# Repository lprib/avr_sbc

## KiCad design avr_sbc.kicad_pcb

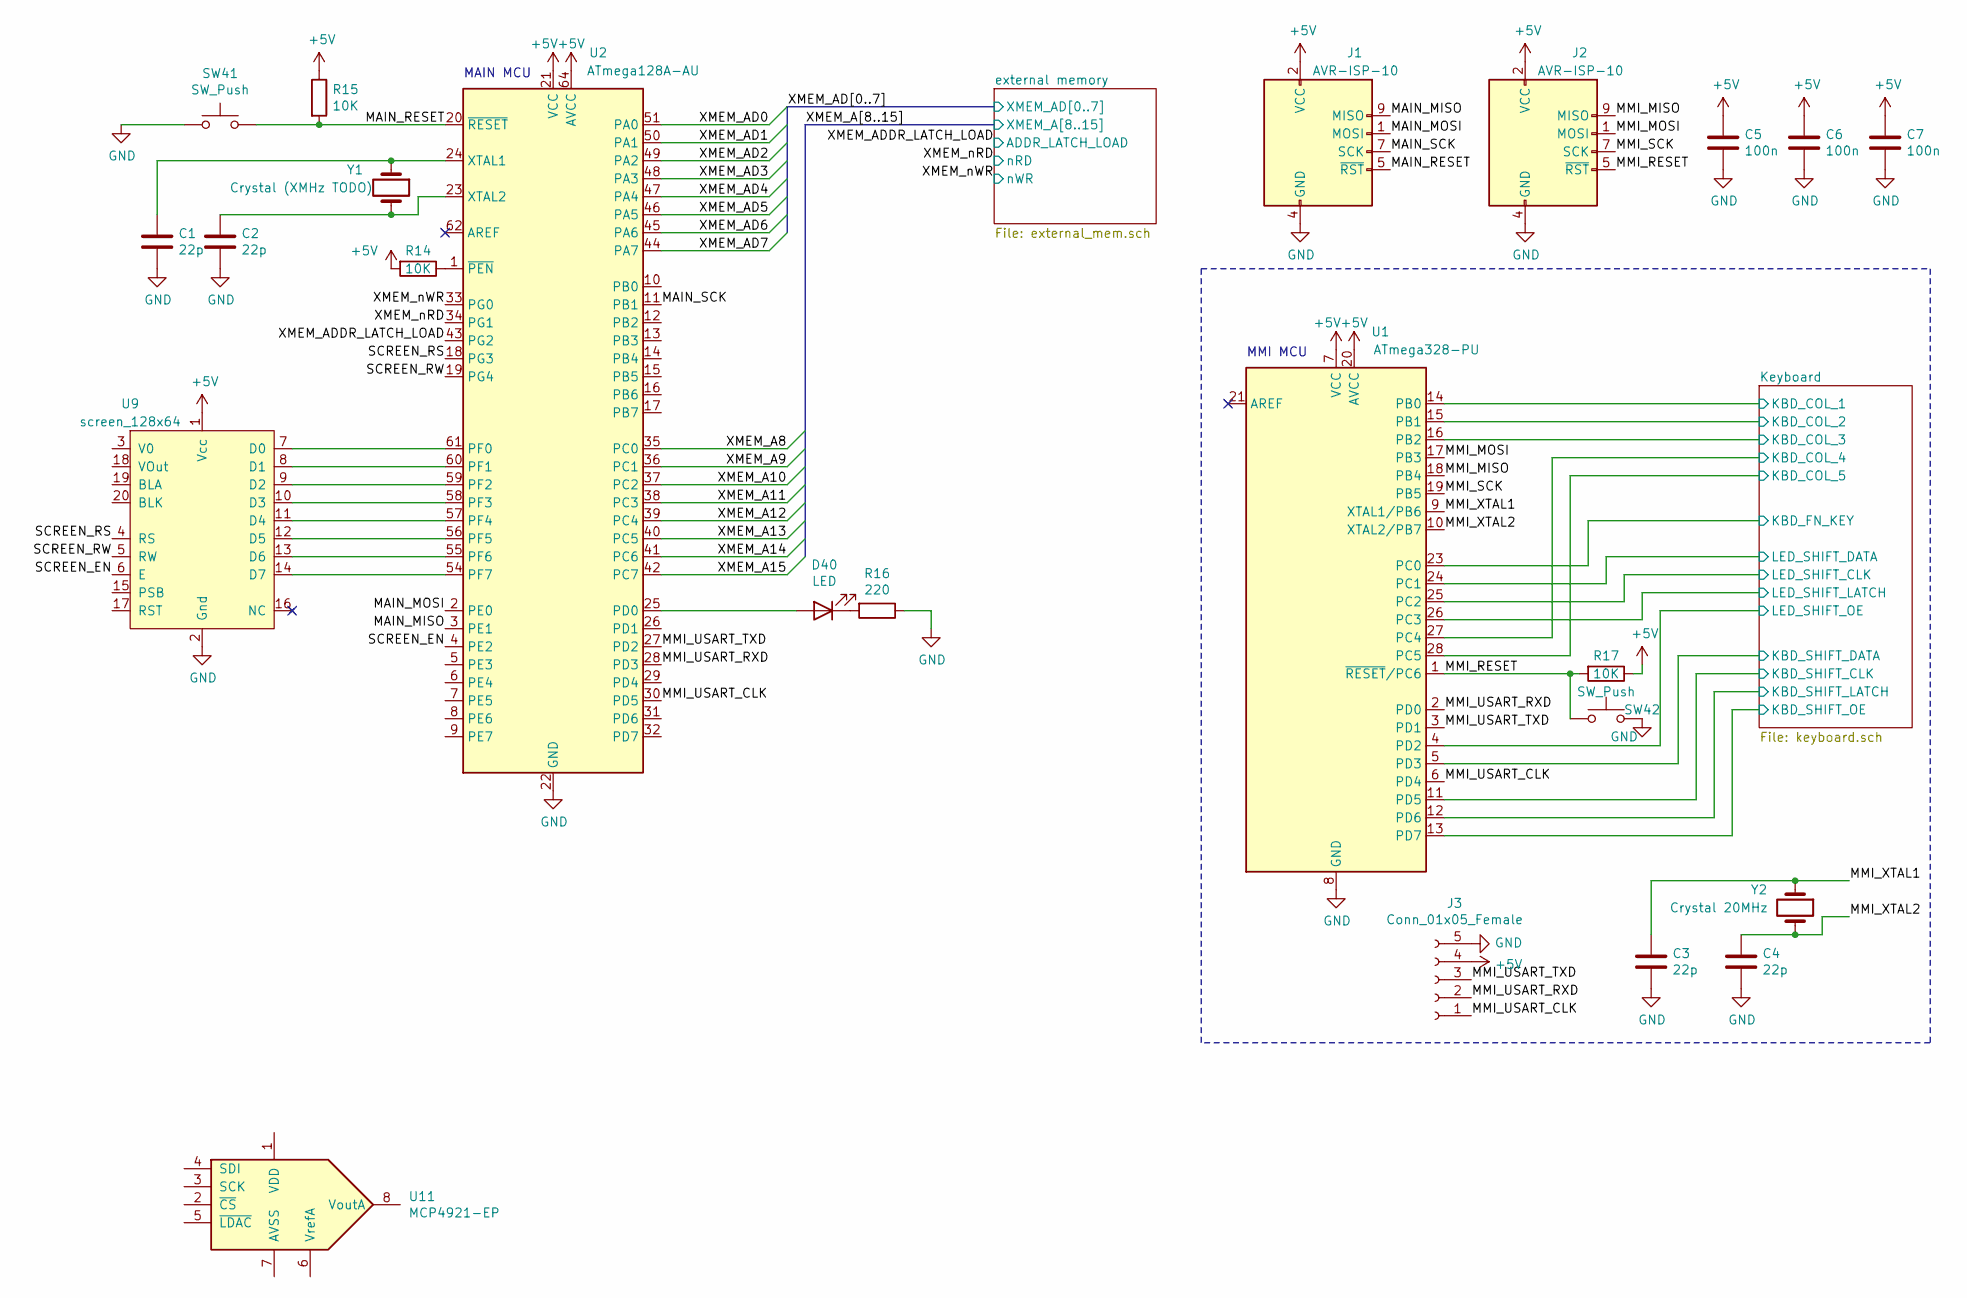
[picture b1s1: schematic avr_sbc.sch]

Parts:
C1, C2, C3, C4: 22p; C_Disc_D3.0mm_W1.6mm_P2.50mm
C5, C6, C7: 100n; C_Disc_D3.0mm_W1.6mm_P2.50mm
D40: LED; LED_D5.0mm
J1, J2: AVR-ISP-10; PinHeader_2x05_P2.54mm_Vertical
J3: Conn_01x05_Female; PinHeader_1x05_P2.54mm_Vertical
R14, R15, R17: 10K; R_Axial_DIN0207_L6.3mm_D2.5mm_P7.62mm_Horizontal
R16: 220; R_Axial_DIN0207_L6.3mm_D2.5mm_P7.62mm_Horizontal
SW41, SW42: SW_Push; SW_PUSH_6mm
U1: ATmega328-PU; DIP-28_W7.62mm
U2: ATmega128A-AU; TQFP-64_14x14mm_P0.8mm
U9: screen_128x64; PinHeader_1x20_P2.54mm_Vertical
U11: MCP4921-EP; DIP-8_W7.62mm
Y1: Crystal (XMHz TODO); Resonator-2Pin_W10.0mm_H5.0mm
Y2: Crystal 20MHz; Resonator-2Pin_W10.0mm_H5.0mm

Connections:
+5V: C5.1, C6.1, C7.1, J1.2 (VCC), J2.2 (VCC), J3.4, R14.2, R15.1, R17.1, U1.7 (VCC), U1.20 (AVCC), U2.21 (VCC), U2.52 (VCC), U2.64 (AVCC), U9.1 (Vcc); also elsewhere on the board
/Keyboard/KBD_COL_1: U1.14 (PB0); also elsewhere on the board
/Keyboard/KBD_COL_2: U1.15 (PB1); also elsewhere on the board
/Keyboard/KBD_COL_3: U1.16 (PB2); also elsewhere on the board
/Keyboard/KBD_COL_4: U1.27 (PC4); also elsewhere on the board
/Keyboard/KBD_COL_5: U1.28 (PC5); also elsewhere on the board
/Keyboard/KBD_FN_KEY: U1.23 (PC0); also elsewhere on the board
/Keyboard/KBD_SHIFT_CLK: U1.11 (PD5); also elsewhere on the board
/Keyboard/KBD_SHIFT_DATA: U1.5 (PD3); also elsewhere on the board
/Keyboard/KBD_SHIFT_LATCH: U1.12 (PD6); also elsewhere on the board
/Keyboard/KBD_SHIFT_OE: U1.13 (PD7); also elsewhere on the board
/Keyboard/LED_SHIFT_CLK: U1.25 (PC2); also elsewhere on the board
/Keyboard/LED_SHIFT_DATA: U1.24 (PC1); also elsewhere on the board
/Keyboard/LED_SHIFT_LATCH: U1.26 (PC3); also elsewhere on the board
/Keyboard/LED_SHIFT_OE: U1.4 (PD2); also elsewhere on the board
/MAIN_MISO: J1.9 (MISO), U2.3 (PE1)
/MAIN_MOSI: J1.1 (MOSI), U2.2 (PE0)
/MAIN_RESET: J1.5 (~RST), R15.2, SW41.2, U2.20 (~RESET)
/MAIN_SCK: J1.7 (SCK), U2.11 (PB1)
/MMI_MISO: J2.9 (MISO), U1.18 (PB4)
/MMI_MOSI: J2.1 (MOSI), U1.17 (PB3)
/MMI_RESET: J2.5 (~RST), R17.2, SW42.1, U1.1 (~RESET~/PC6)
/MMI_SCK: J2.7 (SCK), U1.19 (PB5)
/MMI_USART_CLK: J3.1, U1.6 (PD4), U2.30 (PD5)
/MMI_USART_RXD: J3.2, U1.2 (PD0), U2.28 (PD3)
/MMI_USART_TXD: J3.3, U1.3 (PD1), U2.27 (PD2)
/MMI_XTAL1: C3.2, U1.9 (XTAL1/PB6), Y2.1
/MMI_XTAL2: C4.2, U1.10 (XTAL2/PB7), Y2.2
/SCREEN_EN: U2.4 (PE2), U9.6 (E)
/SCREEN_RS: U2.18 (PG3), U9.4 (RS)
/SCREEN_RW: U2.19 (PG4), U9.5 (RW)
/XMEM_A8: U2.35 (PC0); also elsewhere on the board
/XMEM_A9: U2.36 (PC1); also elsewhere on the board
/XMEM_A10: U2.37 (PC2); also elsewhere on the board
/XMEM_A11: U2.38 (PC3); also elsewhere on the board
/XMEM_A12: U2.39 (PC4); also elsewhere on the board
/XMEM_A13: U2.40 (PC5); also elsewhere on the board
/XMEM_A14: U2.41 (PC6); also elsewhere on the board
/XMEM_A15: U2.42 (PC7); also elsewhere on the board
/XMEM_AD0: U2.51 (PA0); also elsewhere on the board
/XMEM_AD1: U2.50 (PA1); also elsewhere on the board
/XMEM_AD2: U2.49 (PA2); also elsewhere on the board
/XMEM_AD3: U2.48 (PA3); also elsewhere on the board
/XMEM_AD4: U2.47 (PA4); also elsewhere on the board
/XMEM_AD5: U2.46 (PA5); also elsewhere on the board
/XMEM_AD6: U2.45 (PA6); also elsewhere on the board
/XMEM_AD7: U2.44 (PA7); also elsewhere on the board
/XMEM_ADDR_LATCH_LOAD: U2.43 (PG2); also elsewhere on the board
/XMEM_nRD: U2.34 (PG1); also elsewhere on the board
/XMEM_nWR: U2.33 (PG0); also elsewhere on the board
GND: C1.1, C2.1, C3.1, C4.1, C5.2, C6.2, C7.2, J1.4 (GND), J1.6 (GND), J1.8 (GND), J1.10 (GND), J2.4 (GND), J2.6 (GND), J2.8 (GND), J2.10 (GND), J3.5, R16.1, SW41.1, SW42.2, U1.8 (GND), U1.22 (GND), U2.22 (GND), U2.53 (GND), U2.63 (GND), U9.2 (Gnd); also elsewhere on the board
unnamed: C1.2, U2.24 (XTAL1), Y1.1
unnamed: C2.2, U2.23 (XTAL2), Y1.2
unnamed: D40.1 (K), R16.2
unnamed: D40.2 (A), U2.25 (PD0)
unnamed: R14.1, U2.1 (~PEN)
unnamed: U2.54 (PF7), U9.14 (D7)
unnamed: U2.55 (PF6), U9.13 (D6)
unnamed: U2.56 (PF5), U9.12 (D5)
unnamed: U2.57 (PF4), U9.11 (D4)
unnamed: U2.58 (PF3), U9.10 (D3)
unnamed: U2.59 (PF2), U9.9 (D2)
unnamed: U2.60 (PF1), U9.8 (D1)
unnamed: U2.61 (PF0), U9.7 (D0)

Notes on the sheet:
MMI MCU
MAIN MCU

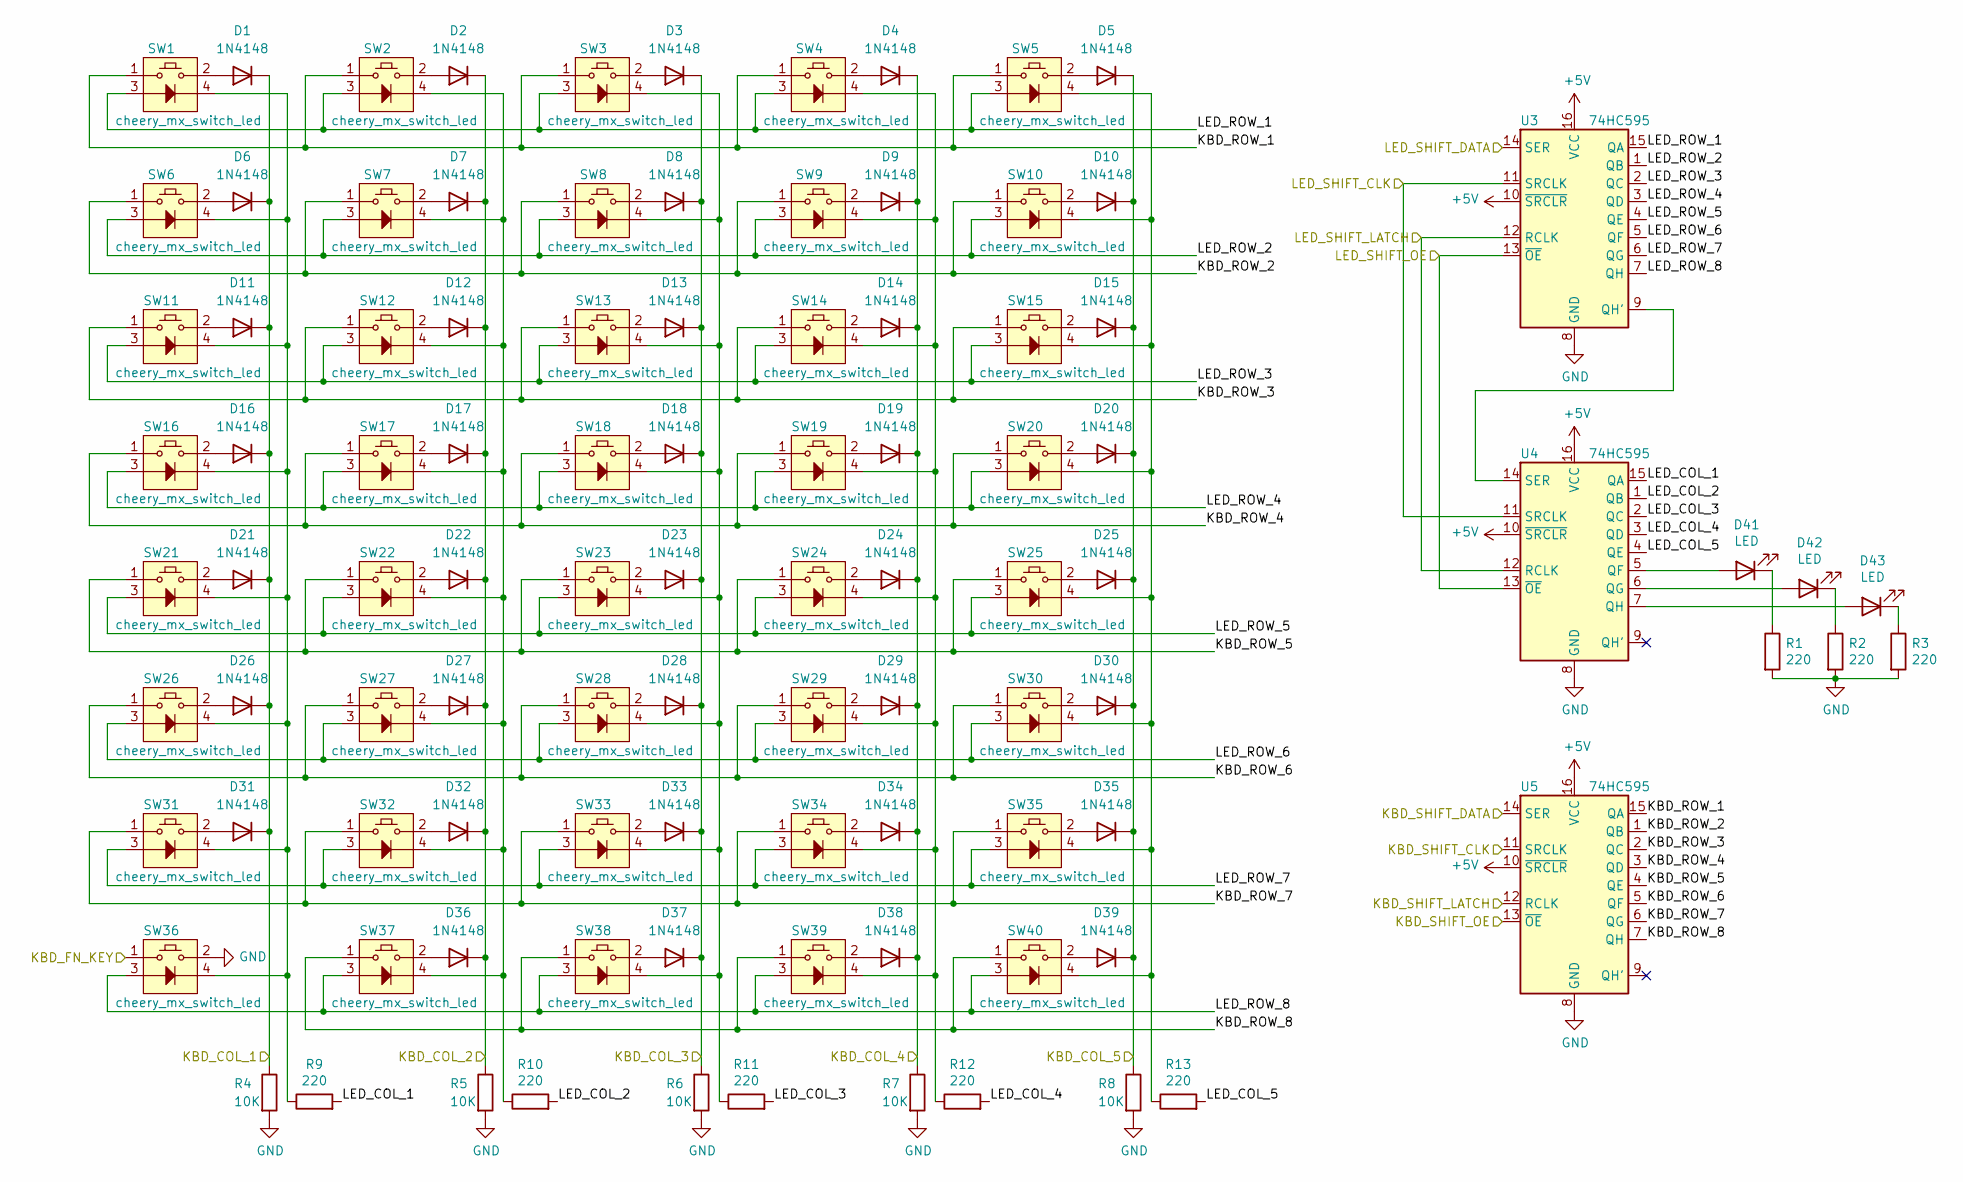
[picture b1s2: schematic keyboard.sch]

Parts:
D1, D2, D3, D4, D5, D6, D7, D8, D9, D10, D11, D12, D13, D14, D15, D16, D17, D18, D19, D20, D21, D22, D23, D24, D25, D26, D27, D28, D29, D30, D31, D32, D33, D34, D35, D36, D37, D38, D39: 1N4148; diode_tht_p5.08mm_horizontal_side_lbl
D41, D42, D43: LED; LED_D5.0mm
R1, R2, R3, R9, R10, R11, R12, R13: 220; R_Axial_DIN0207_L6.3mm_D2.5mm_P7.62mm_Horizontal
R4, R5, R6, R7, R8: 10K; R_Axial_DIN0207_L6.3mm_D2.5mm_P7.62mm_Horizontal
SW1, SW2, SW3, SW4, SW5, SW6, SW7, SW8, SW9, SW10, SW11, SW12, SW13, SW14, SW15, SW16, SW17, SW18, SW19, SW20, SW21, SW22, SW23, SW24, SW25, SW26, SW27, SW28, SW29, SW30, SW31, SW32, SW33, SW34, SW35, SW36, SW37, SW38, SW39, SW40: cheery_mx_switch_led; cherry_mx_switch_with_led
U3, U4, U5: 74HC595; DIP-16_W7.62mm

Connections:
+5V: U3.10 (~SRCLR), U3.16 (VCC), U4.10 (~SRCLR), U4.16 (VCC), U5.10 (~SRCLR), U5.16 (VCC); also elsewhere on the board
/Keyboard/KBD_COL_1: D1.1 (K), D6.1 (K), D11.1 (K), D16.1 (K), D21.1 (K), D26.1 (K), D31.1 (K), R4.1; also elsewhere on the board
/Keyboard/KBD_COL_2: D2.1 (K), D7.1 (K), D12.1 (K), D17.1 (K), D22.1 (K), D27.1 (K), D32.1 (K), D36.1 (K), R5.1; also elsewhere on the board
/Keyboard/KBD_COL_3: D3.1 (K), D8.1 (K), D13.1 (K), D18.1 (K), D23.1 (K), D28.1 (K), D33.1 (K), D37.1 (K), R6.1; also elsewhere on the board
/Keyboard/KBD_COL_4: D4.1 (K), D9.1 (K), D14.1 (K), D19.1 (K), D24.1 (K), D29.1 (K), D34.1 (K), D38.1 (K), R7.1; also elsewhere on the board
/Keyboard/KBD_COL_5: D5.1 (K), D10.1 (K), D15.1 (K), D20.1 (K), D25.1 (K), D30.1 (K), D35.1 (K), D39.1 (K), R8.1; also elsewhere on the board
/Keyboard/KBD_FN_KEY: SW36.1; also elsewhere on the board
/Keyboard/KBD_ROW_1: SW1.1, SW2.1, SW3.1, SW4.1, SW5.1, U5.15 (QA)
/Keyboard/KBD_ROW_2: SW6.1, SW7.1, SW8.1, SW9.1, SW10.1, U5.1 (QB)
/Keyboard/KBD_ROW_3: SW11.1, SW12.1, SW13.1, SW14.1, SW15.1, U5.2 (QC)
/Keyboard/KBD_ROW_4: SW16.1, SW17.1, SW18.1, SW19.1, SW20.1, U5.3 (QD)
/Keyboard/KBD_ROW_5: SW21.1, SW22.1, SW23.1, SW24.1, SW25.1, U5.4 (QE)
/Keyboard/KBD_ROW_6: SW26.1, SW27.1, SW28.1, SW29.1, SW30.1, U5.5 (QF)
/Keyboard/KBD_ROW_7: SW31.1, SW32.1, SW33.1, SW34.1, SW35.1, U5.6 (QG)
/Keyboard/KBD_ROW_8: SW37.1, SW38.1, SW39.1, SW40.1, U5.7 (QH)
/Keyboard/KBD_SHIFT_CLK: U5.11 (SRCLK); also elsewhere on the board
/Keyboard/KBD_SHIFT_DATA: U5.14 (SER); also elsewhere on the board
/Keyboard/KBD_SHIFT_LATCH: U5.12 (RCLK); also elsewhere on the board
/Keyboard/KBD_SHIFT_OE: U5.13 (~OE); also elsewhere on the board
/Keyboard/LED_COL_1: R9.2, U4.15 (QA)
/Keyboard/LED_COL_2: R10.2, U4.1 (QB)
/Keyboard/LED_COL_3: R11.2, U4.2 (QC)
/Keyboard/LED_COL_4: R12.2, U4.3 (QD)
/Keyboard/LED_COL_5: R13.2, U4.4 (QE)
/Keyboard/LED_ROW_1: SW1.3, SW2.3, SW3.3, SW4.3, SW5.3, U3.15 (QA)
/Keyboard/LED_ROW_2: SW6.3, SW7.3, SW8.3, SW9.3, SW10.3, U3.1 (QB)
/Keyboard/LED_ROW_3: SW11.3, SW12.3, SW13.3, SW14.3, SW15.3, U3.2 (QC)
/Keyboard/LED_ROW_4: SW16.3, SW17.3, SW18.3, SW19.3, SW20.3, U3.3 (QD)
/Keyboard/LED_ROW_5: SW21.3, SW22.3, SW23.3, SW24.3, SW25.3, U3.4 (QE)
/Keyboard/LED_ROW_6: SW26.3, SW27.3, SW28.3, SW29.3, SW30.3, U3.5 (QF)
/Keyboard/LED_ROW_7: SW31.3, SW32.3, SW33.3, SW34.3, SW35.3, U3.6 (QG)
/Keyboard/LED_ROW_8: SW36.3, SW37.3, SW38.3, SW39.3, SW40.3, U3.7 (QH)
/Keyboard/LED_SHIFT_CLK: U3.11 (SRCLK), U4.11 (SRCLK); also elsewhere on the board
/Keyboard/LED_SHIFT_DATA: U3.14 (SER); also elsewhere on the board
/Keyboard/LED_SHIFT_LATCH: U3.12 (RCLK), U4.12 (RCLK); also elsewhere on the board
/Keyboard/LED_SHIFT_OE: U3.13 (~OE), U4.13 (~OE); also elsewhere on the board
GND: R1.2, R2.2, R3.2, R4.2, R5.2, R6.2, R7.2, R8.2, SW36.2, U3.8 (GND), U4.8 (GND), U5.8 (GND); also elsewhere on the board
unnamed: D1.2 (A), SW1.2
unnamed: D2.2 (A), SW2.2
unnamed: D3.2 (A), SW3.2
unnamed: D4.2 (A), SW4.2
unnamed: D5.2 (A), SW5.2
unnamed: D6.2 (A), SW6.2
unnamed: D7.2 (A), SW7.2
unnamed: D8.2 (A), SW8.2
unnamed: D9.2 (A), SW9.2
unnamed: D10.2 (A), SW10.2
unnamed: D11.2 (A), SW11.2
unnamed: D12.2 (A), SW12.2
unnamed: D13.2 (A), SW13.2
unnamed: D14.2 (A), SW14.2
unnamed: D15.2 (A), SW15.2
unnamed: D16.2 (A), SW16.2
unnamed: D17.2 (A), SW17.2
unnamed: D18.2 (A), SW18.2
unnamed: D19.2 (A), SW19.2
unnamed: D20.2 (A), SW20.2
unnamed: D21.2 (A), SW21.2
unnamed: D22.2 (A), SW22.2
unnamed: D23.2 (A), SW23.2
unnamed: D24.2 (A), SW24.2
unnamed: D25.2 (A), SW25.2
unnamed: D26.2 (A), SW26.2
unnamed: D27.2 (A), SW27.2
unnamed: D28.2 (A), SW28.2
unnamed: D29.2 (A), SW29.2
unnamed: D30.2 (A), SW30.2
unnamed: D31.2 (A), SW31.2
unnamed: D32.2 (A), SW32.2
unnamed: D33.2 (A), SW33.2
unnamed: D34.2 (A), SW34.2
unnamed: D35.2 (A), SW35.2
unnamed: D36.2 (A), SW37.2
unnamed: D37.2 (A), SW38.2
unnamed: D38.2 (A), SW39.2
unnamed: D39.2 (A), SW40.2
unnamed: D41.1 (K), R1.1
unnamed: D41.2 (A), U4.5 (QF)
unnamed: D42.1 (K), R2.1
unnamed: D42.2 (A), U4.6 (QG)
unnamed: D43.1 (K), R3.1
unnamed: D43.2 (A), U4.7 (QH)
unnamed: R9.1, SW1.4, SW6.4, SW11.4, SW16.4, SW21.4, SW26.4, SW31.4, SW36.4
unnamed: R10.1, SW2.4, SW7.4, SW12.4, SW17.4, SW22.4, SW27.4, SW32.4, SW37.4
unnamed: R11.1, SW3.4, SW8.4, SW13.4, SW18.4, SW23.4, SW28.4, SW33.4, SW38.4
unnamed: R12.1, SW4.4, SW9.4, SW14.4, SW19.4, SW24.4, SW29.4, SW34.4, SW39.4
unnamed: R13.1, SW5.4, SW10.4, SW15.4, SW20.4, SW25.4, SW30.4, SW35.4, SW40.4
unnamed: U3.9 (QH'), U4.14 (SER)

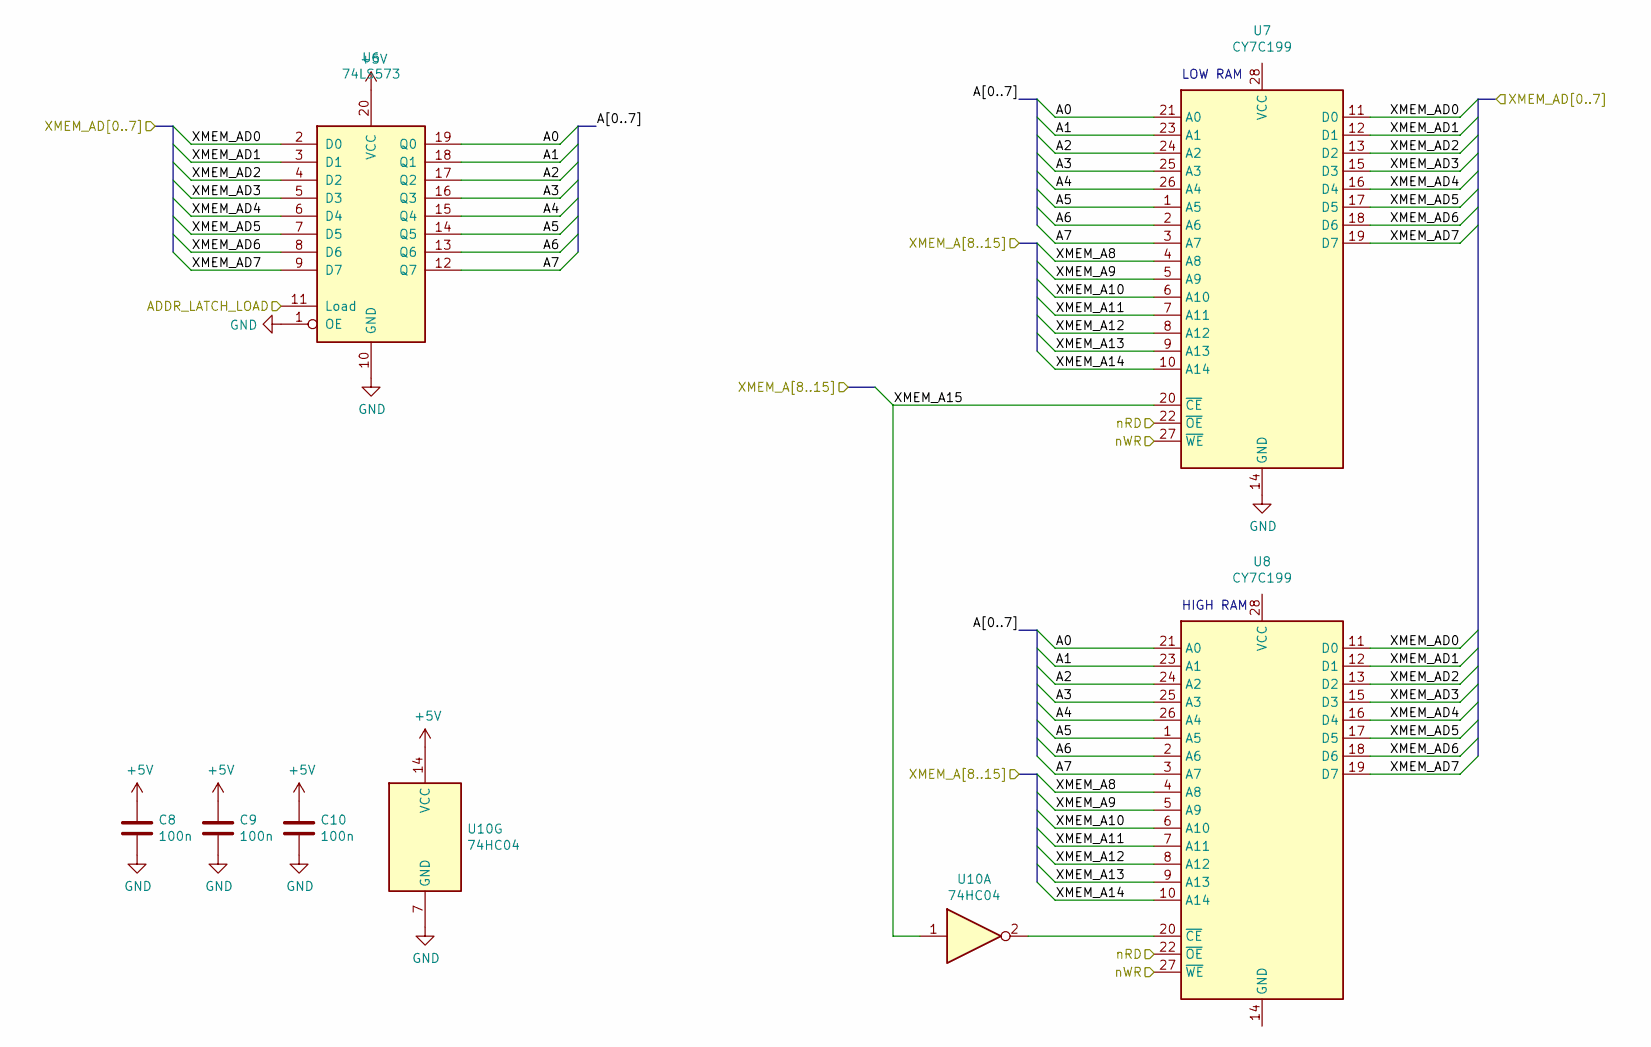
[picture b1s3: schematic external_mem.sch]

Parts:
C8, C9, C10: 100n; C_Disc_D3.0mm_W1.6mm_P2.50mm
U6: 74LS573; DIP-20_W7.62mm
U7, U8: CY7C199; DIP-28_W7.62mm
U10: 74HC04; DIP-14_W7.62mm

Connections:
+5V: C8.2, C9.2, C10.2, U6.20 (VCC), U10.14 (VCC); also elsewhere on the board
/XMEM_A8: U7.4 (A8), U8.4 (A8); also elsewhere on the board
/XMEM_A9: U7.5 (A9), U8.5 (A9); also elsewhere on the board
/XMEM_A10: U7.6 (A10), U8.6 (A10); also elsewhere on the board
/XMEM_A11: U7.7 (A11), U8.7 (A11); also elsewhere on the board
/XMEM_A12: U7.8 (A12), U8.8 (A12); also elsewhere on the board
/XMEM_A13: U7.9 (A13), U8.9 (A13); also elsewhere on the board
/XMEM_A14: U7.10 (A14), U8.10 (A14); also elsewhere on the board
/XMEM_A15: U7.20 (~CE~), U10.1; also elsewhere on the board
/XMEM_AD0: U6.2 (D0), U7.11 (D0), U8.11 (D0); also elsewhere on the board
/XMEM_AD1: U6.3 (D1), U7.12 (D1), U8.12 (D1); also elsewhere on the board
/XMEM_AD2: U6.4 (D2), U7.13 (D2), U8.13 (D2); also elsewhere on the board
/XMEM_AD3: U6.5 (D3), U7.15 (D3), U8.15 (D3); also elsewhere on the board
/XMEM_AD4: U6.6 (D4), U7.16 (D4), U8.16 (D4); also elsewhere on the board
/XMEM_AD5: U6.7 (D5), U7.17 (D5), U8.17 (D5); also elsewhere on the board
/XMEM_AD6: U6.8 (D6), U7.18 (D6), U8.18 (D6); also elsewhere on the board
/XMEM_AD7: U6.9 (D7), U7.19 (D7), U8.19 (D7); also elsewhere on the board
/XMEM_ADDR_LATCH_LOAD: U6.11 (Load); also elsewhere on the board
/XMEM_nRD: U7.22 (~OE~), U8.22 (~OE~); also elsewhere on the board
/XMEM_nWR: U7.27 (~WE~), U8.27 (~WE~); also elsewhere on the board
/external memory/A0: U6.19 (Q0), U7.21 (A0), U8.21 (A0)
/external memory/A1: U6.18 (Q1), U7.23 (A1), U8.23 (A1)
/external memory/A2: U6.17 (Q2), U7.24 (A2), U8.24 (A2)
/external memory/A3: U6.16 (Q3), U7.25 (A3), U8.25 (A3)
/external memory/A4: U6.15 (Q4), U7.26 (A4), U8.26 (A4)
/external memory/A5: U6.14 (Q5), U7.1 (A5), U8.1 (A5)
/external memory/A6: U6.13 (Q6), U7.2 (A6), U8.2 (A6)
/external memory/A7: U6.12 (Q7), U7.3 (A7), U8.3 (A7)
GND: C8.1, C9.1, C10.1, U6.1 (OE), U6.10 (GND), U7.14 (GND), U10.7 (GND); also elsewhere on the board
unnamed: U8.20 (~CE~), U10.2

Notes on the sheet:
LOW RAM
HIGH RAM

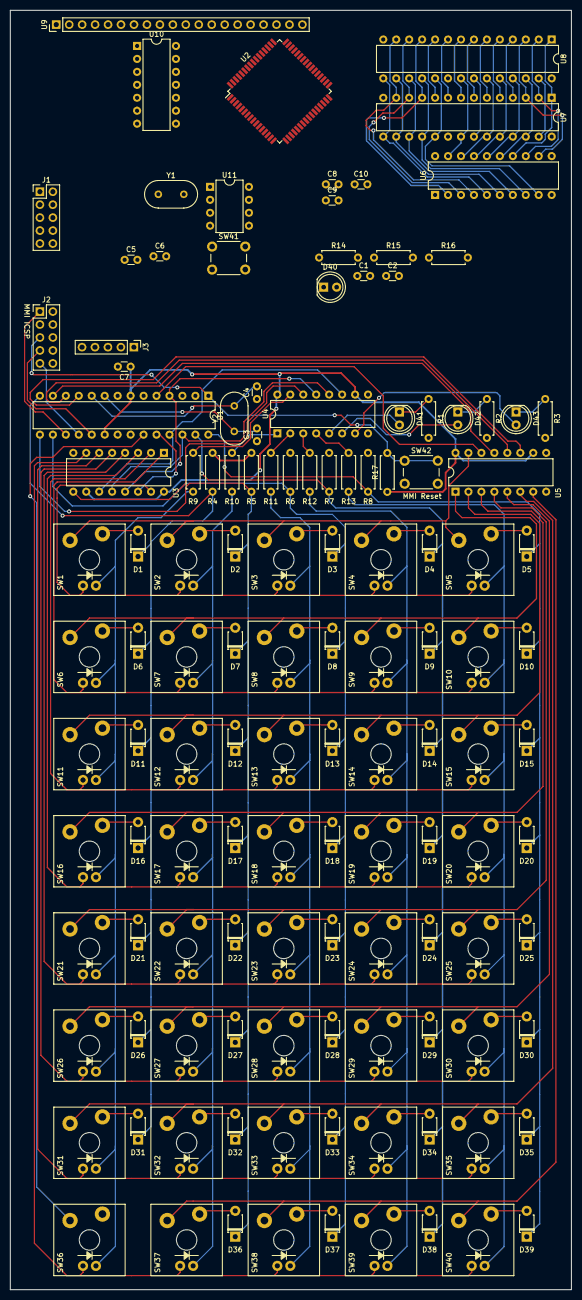
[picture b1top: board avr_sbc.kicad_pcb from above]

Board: 2 copper layers, 110.0 x 250.8 mm, 128 parts (0 on the bottom side), 145 nets.

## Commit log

2021-03-29 atmega128 and external memory
2021-03-29 project rename
2021-03-29 route icsp and reset button for MMI MCU
